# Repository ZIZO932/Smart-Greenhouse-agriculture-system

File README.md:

# Smart Greenhouse

A greenhouse prototype I built to monitor growing conditions and control pumps, fans, lighting, and temperature hardware. I used sweet basil as the main crop for testing.

The project changed quite a bit between the CAD and the assembled version. The original design used a Raspberry Pi Pico W, and I switched to an ESP32 during the build after damaging the Pico. Both versions are kept in this repo.

## Why I built it

I wanted to connect sensor readings to something the greenhouse could actually do: water the soil, switch on a fan, or adjust the lights. Fitting the tanks, pumps, electronics, and growing bed into one structure was a big part of the work too.

## The layout

The design has three main stacked sections, plus a camera track around the top:

- **Tanks and pumps:** a 5 L water tank and three 1 L nutrient tanks, each with its own pumping line.
- **Electronics:** the controller, power distribution, sensor connections, and relay circuitry.
- **Growing bed:** the soil and plants, with tubing routed up from the tanks.
- **Camera track:** a planned moving camera platform for taking pictures around the plants.

The CAD used a transparent bed. For the physical prototype, I built the frame from MDF and used a polyethylene cover for the growing layer.

[CAD files](CAD/) include the assembly and a ZIP archive. The larger STEP model is also [on Google Drive](https://drive.google.com/file/d/1caedlcHiUJ2DHqxGwvVZIDkTWpKjw0eq/view?usp=drive_link).

## Electronics

The original PCB design uses a ULN2803A to drive the relays, with separate power rails for the controller, sensors, and higher-power hardware. The sensor setup includes a BH1750 light sensor, DS18B20 temperature sensing, capacitive soil moisture sensing, and an RS-485 connection for an NPK sensor through a MAX485.

I had to fix relay footprints and adjust the routing while working through the board design.

## Building it

The first frame used nails and didn't hold the weight properly. I rebuilt the joints with screws, then routed the pumps and tubing through the layers.

I assembled the regulated power supply and wired the sensors and relay-controlled hardware. This was also where I damaged the Pico and moved to the ESP32. My build notes record a six-hour integrated test of the sensors and actuators.

## Dashboard and code

The dashboard work uses MQTT, Flask, and MySQL to collect and display readings. Grafana is shown in the build documentation too.

There are a few different stages in the uploaded code:

| File or folder | What it contains |
| --- | --- |
| [Firmware/main.py](Firmware/main.py) | Pico MicroPython code for sensor reading, relay control, and UART communication with a Pi Zero |
| [website/app.py](website/app.py) | Flask app that receives MQTT messages, stores readings in MySQL, and serves dashboard endpoints |
| [website/final_code_10204.ino](website/final_code_10204.ino) | ESP32 code excerpt with sensor functions, relay helpers, and plant profiles |
| [code parts](code%20parts/) | Other Arduino and MQTT snippets from development |
| [templates](templates/) | Dashboard HTML |

The ESP32 excerpt currently generates sample NPK values in `updateFakeNPK()`. Those values aren't live nutrient measurements. It also doesn't include `setup()` and `loop()`, so the uploaded excerpt isn't a complete flashable sketch.

The Flask app expects `templates/index.html` next to the app, while the uploaded HTML is named `templates/index (1).html` at the repo root. That path needs matching before running the dashboard locally. Broker addresses and database settings also need to match the local setup.

## Camera and disease detection

I planned a Pi Zero 2 W and Camera V2 platform that moves around the plants, takes images, and parks between scans. The proposed scan interval was 30 minutes, with a model trained using the [New Plant Diseases Dataset](https://www.kaggle.com/datasets/vipoooool/new-plant-diseases-dataset).

The repo doesn't include trained model files or disease-detection results yet. This part is documented as a planned extension of the monitoring system.

## Original parts estimate

This is the parts list from the original design stage, including the Pico and camera hardware. Prices are recorded estimates from that stage.

| Name | Cost Per Item (USD) | Quantity | Total (USD) | Link | Distributor |
| :--- | :--- | :--- | :--- | :--- | :--- |
| **Water pump** | 5.57 | 4 | 22.28 | [Link](https://www.ram-e-shop.com/shop/dc-pump-240l-water-pump12vdc-ultra-quiet-brushless-240l-h-7953) | Ram Electronics |
| **PCB Fabrication** | 5.74 | 1 | 5.74 | [Link](https://jlcpcb.com) | JLCPCB |
| **Pin Header 1x04** | 0.12 | 2 | 0.24 | [Link](https://makerselectronics.com/product/pin-headers-male-2-54mm-5pin-straight-black-11mm/) | Makers Electronics |
| **Pin Header 1x02** | 0.10 | 7 | 0.67 | [Link](https://makerselectronics.com/product/pin-headers-male-2-54mm-5pin-straight-black-11mm/) | Makers Electronics |
| **Ceramic Cap** | 0.04 | 10 | 0.38 | [Link](https://makerselectronics.com/product/ceramic-capacitor-100nf-50v/) | Makers Electronics |
| **Electrolytic Cap** | 0.10 | 4 | 0.40 | [Link](https://makerselectronics.com/product/capacitor-10uf-25v-4x7mm/) | Makers Electronics |
| **Resistor** | 0.04 | 10 | 0.40 | [Link](https://makerselectronics.com/product/carbon-resistor-10k%cf%89-2w-through-hole/) | Makers Electronics |
| **12V 5A Power Adapter** | 5.74 | 1 | 5.74 | [Link](https://makerselectronics.com/product/adapter-12v-3a-3/) | Makers Electronics |
| **Barrel Jack** | 0.29 | 1 | 0.29 | [Link](https://store.fut-electronics.com/products/dc-barrel-female-jack?_pos=2&_sid=9cbb68bec&_ss=r) | Future Electronics Egypt |
| **DIP-18 Socket** | 3.16 | 1 | 3.16 | [Link](https://store.fut-electronics.com/search?type=product&q=DIP-18+7.62mm) | Future Electronics Egypt |
| **Relay** | 1.34 | 7 | 9.38 | [Link](https://www.amazon.eg/-/en/Generic-12V-Relay-SRD-12VDC-SL-C-Automatic/dp/B09GNYCBJ8) | Amazon Egypt |
| **Schottky Diode** | 0.15 | 1 | 0.15 | [Link](https://store.fut-electronics.com/products/copy-of-diode-1n5408-3a-1000v-high-current-rectifier?_pos=1&_sid=7c0e00b0d&_ss=r) | Future Electronics Egypt |
| **Inductor** | 0.02 | 1 | 0.02 | [Link](https://makerselectronics.com/product/inductor-330uh-0510-1w/?srsltid=AfmBOopEyPfXRbjQeAZuTj9z0SJHXyytV2tzQKyfccnhfVPX7rr7i2Ne) | Makers Electronics Egypt |
| **NPK Soil Sensor** | 61.26 | 1 | 61.26 | [Link](https://store.fut-electronics.com/products/soil-npk-nitrogen-phosphorus-potassium-nutrient-sensor?_pos=1&_sid=cc849b4cb&_ss=r) | Future Electronics Egypt |
| **Soil Moisture Sensor** | 1.91 | 1 | 1.91 | [Link](https://www.ram-e-shop.com/shop/sen-soil-c-capacitive-analog-soil-moisture-sensor-v2-0-sku-soil-c-8116?srsltid=AfmBOookvggy4W1wl8oSb-pGGNBmixARQOTydpFUzx5W_-lss_Y-4-94) | RAM Electronics |
| **Light Sensor** | 3.73 | 1 | 3.73 | [Link](https://store.fut-electronics.com/products/digital-light-intensity-module) | Future Electronics Egypt |
| **Temp Sensor (air)** | 0.86 | 1 | 0.86 | [Link](https://makerselectronics.com/product/ds18b20-temperature-sensor-to-92/) | Makers Electronics Egypt |
| **Temp Sensor (soil)** | 1.63 | 1 | 1.63 | [Link](https://www.ram-e-shop.com/ar/shop/wire-ds18b20-ds18b20-waterproof-temperature-sensor-original-chip-7175) | RAM Electronics |
| **Darlington Driver** | 0.46 | 1 | 0.46 | [Link](https://makerselectronics.com/product/uln2803apg-darlington-transistor-arrays-dip-18-brand-toshiba/) | Makers Electronics |
| **RS485 Transceiver** | 0.55 | 1 | 0.55 | [Link](https://uge-one.com/product/max485-rs-485-transceiver-dip8/) | UGE Electronics Egypt |
| **Raspberry Pi Camera V2** | 15.31 | 1 | 15.31 | [Link](https://www.ram-e-shop.com/ar/shop/rpi-v2-camera-raspberry-pi-camera-module-v2-official-8-mp-hd-imx219-official-6887) | Ram Electronics |
| **LDO Regulator** | 0.06 | 1 | 0.06 | [Link](https://www.ram-e-shop.com/ar/shop/lt1117-3-3v-ams1117-3-3v-6628) | Ram Electronics Egypt |
| **Buck Converter IC** | 0.77 | 1 | 0.77 | [Link](https://makerselectronics.com/product/lm2596t-5-0-buck-fixed-40v-5v-3a-to-220-5l-dc-dc-converters-dip-ic/) | Makers Electronics Egypt |
| **Raspberry Pi Zero 2W** | 38.28 | 1 | 38.28 | [Link](https://devboardsmarket.com/products/raspberry-pi-zero-2-w) | DEV boards |
| **Raspberry Pi Pico W** | 16.27 | 1 | 16.27 | [Link](https://www.ram-e-shop.com/ar/shop/rpi-pico-w-raspberry-pi-pico-w-wifi-8524) | RAM electronics |
| **GRAND TOTAL** | | | **$189.94** | | |

## More files

- [Circuit, PCB, and Gerber files](Circuit%20%28Schematic%20and%20pcb%29/)
- [BOM](BOM.csv)
- [Build journal](JOURNAL%20%285%29.md)
- [Database schema](website/database.sql)

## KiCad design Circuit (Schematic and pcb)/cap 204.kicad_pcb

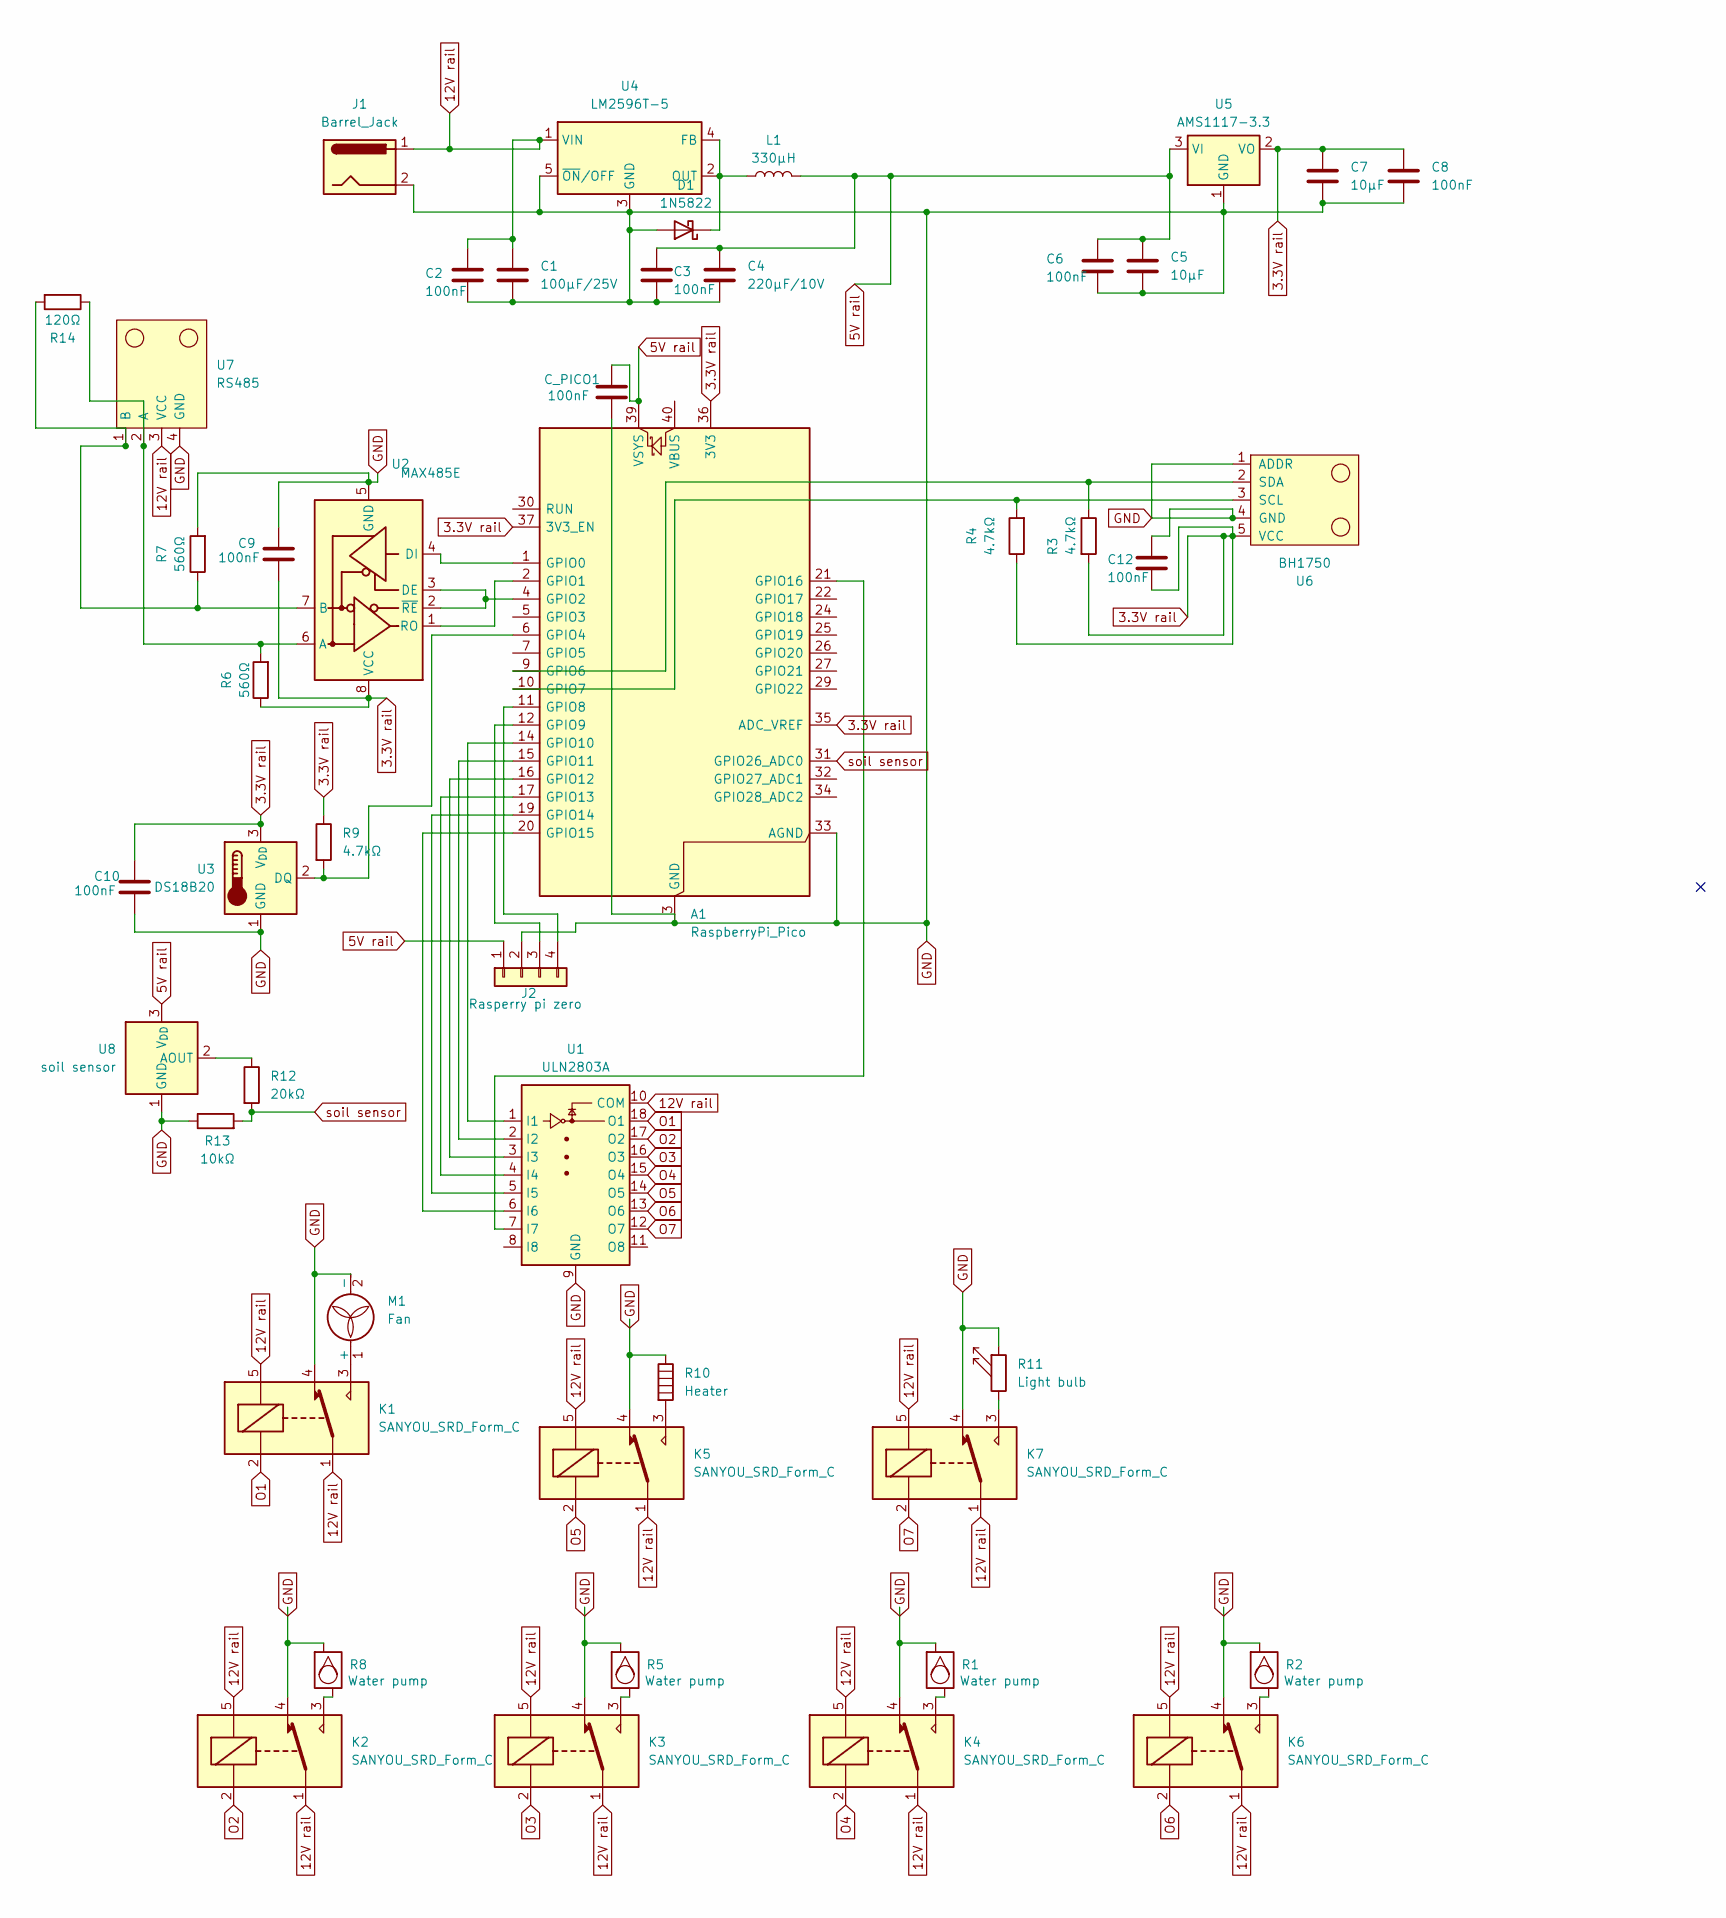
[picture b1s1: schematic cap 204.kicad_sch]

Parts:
A1: RaspberryPi_Pico; RaspberryPi_Pico_Common_Unspecified
C1: 100µF/25V; CP_Radial_D6.3mm_P2.50mm
C2, C3, C6, C8, C9, C10, C12: 100nF; C_Disc_D3.0mm_W1.6mm_P2.50mm
C4: 220µF/10V; CP_Radial_D8.0mm_P3.50mm
C5, C7: 10µF; CP_Radial_D5.0mm_P2.50mm
C_PICO1: 100nF; C_Disc_D3.0mm_W1.6mm_P2.50mm
D1: 1N5822; D_DO-201AD_P15.24mm_Horizontal
J1: Barrel_Jack; L_Axial_L7.0mm_D3.3mm_P10.16mm_Horizontal_Fastron_MICC
J2: Rasperry pi zero; PinHeader_1x04_P2.54mm_Vertical
K1, K2, K3, K4, K5, K6, K7: SANYOU_SRD_Form_C; Relay_SPDT_SANYOU_SRD_Series_Form_C
L1: 330µH; L_Axial_L7.0mm_D3.3mm_P10.16mm_Horizontal_Fastron_MICC
M1: Fan; PinHeader_1x02_P2.54mm_Vertical
R1, R2, R5, R8: Water pump; PinHeader_1x02_P2.54mm_Vertical
R3, R4, R9: 4.7kΩ; R_Axial_DIN0204_L3.6mm_D1.6mm_P7.62mm_Horizontal
R6, R7: 560Ω; R_Axial_DIN0204_L3.6mm_D1.6mm_P7.62mm_Horizontal
R10: Heater; PinHeader_1x02_P2.54mm_Vertical
R11: Light bulb; PinHeader_1x02_P2.54mm_Vertical
R12: 20kΩ; R_Axial_DIN0204_L3.6mm_D1.6mm_P7.62mm_Horizontal
R13: 10kΩ; R_Axial_DIN0204_L3.6mm_D1.6mm_P7.62mm_Horizontal
R14: 120Ω; R_Axial_DIN0204_L3.6mm_D1.6mm_P7.62mm_Horizontal
U1: ULN2803A; DIP-18_W7.62mm
U2: MAX485E; SOIC-8_3.9x4.9mm_P1.27mm
U3: DS18B20; TO-92_Inline
U4: LM2596T-5; TO-220-5_P3.4x3.7mm_StaggerOdd_Lead3.8mm_Vertical
U5: AMS1117-3.3; SOT-223-3_TabPin2
U6: BH1750; module_bh1750
U7: RS485; PinHeader_1x04_P2.54mm_Vertical
U8: soil sensor; TO-92_Inline

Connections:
3.3V rail: A1.35 (ADC_VREF), A1.36 (3V3), A1.37 (3V3_EN), C7.1, C8.1, C9.2, C10.1, C12.2, R3.2, R4.1, R6.1, R9.1, U2.8 (VCC), U3.3 (V_{DD}), U5.2 (VO), U6.5 (VCC)
5V rail: A1.39 (VSYS), C3.1, C4.1, C5.1, C6.1, C_PICO1.1, J2.1, L1.2, U5.3 (VI), U8.3 (V_{DD})
12V rail: C1.1, C2.1, J1.1, K1.1, K1.5, K2.1, K2.5, K3.1, K3.5, K4.1, K4.5, K5.1, K5.5, K6.1, K6.5, K7.1, K7.5, U1.10 (COM), U4.1 (VIN), U7.3 (VCC)
GND: A1.3 (GND), A1.8 (GND), A1.13 (GND), A1.18 (GND), A1.23 (GND), A1.28 (GND), A1.33 (AGND), A1.38 (GND), C1.2, C2.2, C3.2, C4.2, C5.2, C6.2, C7.2, C8.2, C9.1, C10.2, C12.1, C_PICO1.2, D1.2 (A), J1.2, J2.2, K1.4, K2.4, K3.4, K4.4, K5.4, K6.4, K7.4, M1.2 (-), R1.1, R2.1, R5.1, R7.2, R8.1, R10.1, R11.1, R13.1, U1.9 (GND), U2.5 (GND), U3.1 (GND), U4.3 (GND), U4.5 (~ON/OFF), U5.1 (GND), U6.1 (ADDR), U6.4 (GND), U7.4 (GND), U8.1 (GND)
unnamed: A1.1 (GPIO0), U2.4 (DI)
unnamed: A1.2 (GPIO1), U2.1 (RO)
unnamed: A1.4 (GPIO2), U2.2 (~RE), U2.3 (DE)
unnamed: A1.6 (GPIO4), R9.2, U3.2 (DQ)
unnamed: A1.9 (GPIO6), R3.1, U6.2 (SDA)
unnamed: A1.10 (GPIO7), R4.2, U6.3 (SCL)
unnamed: A1.11 (GPIO8), J2.4
unnamed: A1.12 (GPIO9), J2.3
unnamed: A1.14 (GPIO10), U1.1 (I1)
unnamed: A1.15 (GPIO11), U1.2 (I2)
unnamed: A1.16 (GPIO12), U1.3 (I3)
unnamed: A1.17 (GPIO13), U1.4 (I4)
unnamed: A1.19 (GPIO14), U1.5 (I5)
unnamed: A1.20 (GPIO15), U1.6 (I6)
unnamed: A1.21 (GPIO16), U1.7 (I7)
unnamed: D1.1 (K), L1.1, U4.2 (OUT), U4.4 (FB)
unnamed: K2.3, R8.2
unnamed: K3.3, R5.2
unnamed: K4.3, R1.2
unnamed: K5.3, R10.2
unnamed: K6.3, R2.2
unnamed: K7.3, R11.2
unnamed: K1.3, M1.1 (+)
unnamed: R6.2, R14.1, U2.6 (A), U7.2 (A)
unnamed: R7.1, R14.2, U2.7 (B), U7.1 (B)
unnamed: R12.1, U8.2 (AOUT)
O1: K1.2, U1.18 (O1)
O2: K2.2, U1.17 (O2)
O3: K3.2, U1.16 (O3)
O4: K4.2, U1.15 (O4)
O5: K5.2, U1.14 (O5)
O6: K6.2, U1.13 (O6)
O7: K7.2, U1.12 (O7)
soil sensor: A1.31 (GPIO26_ADC0), R12.2, R13.2

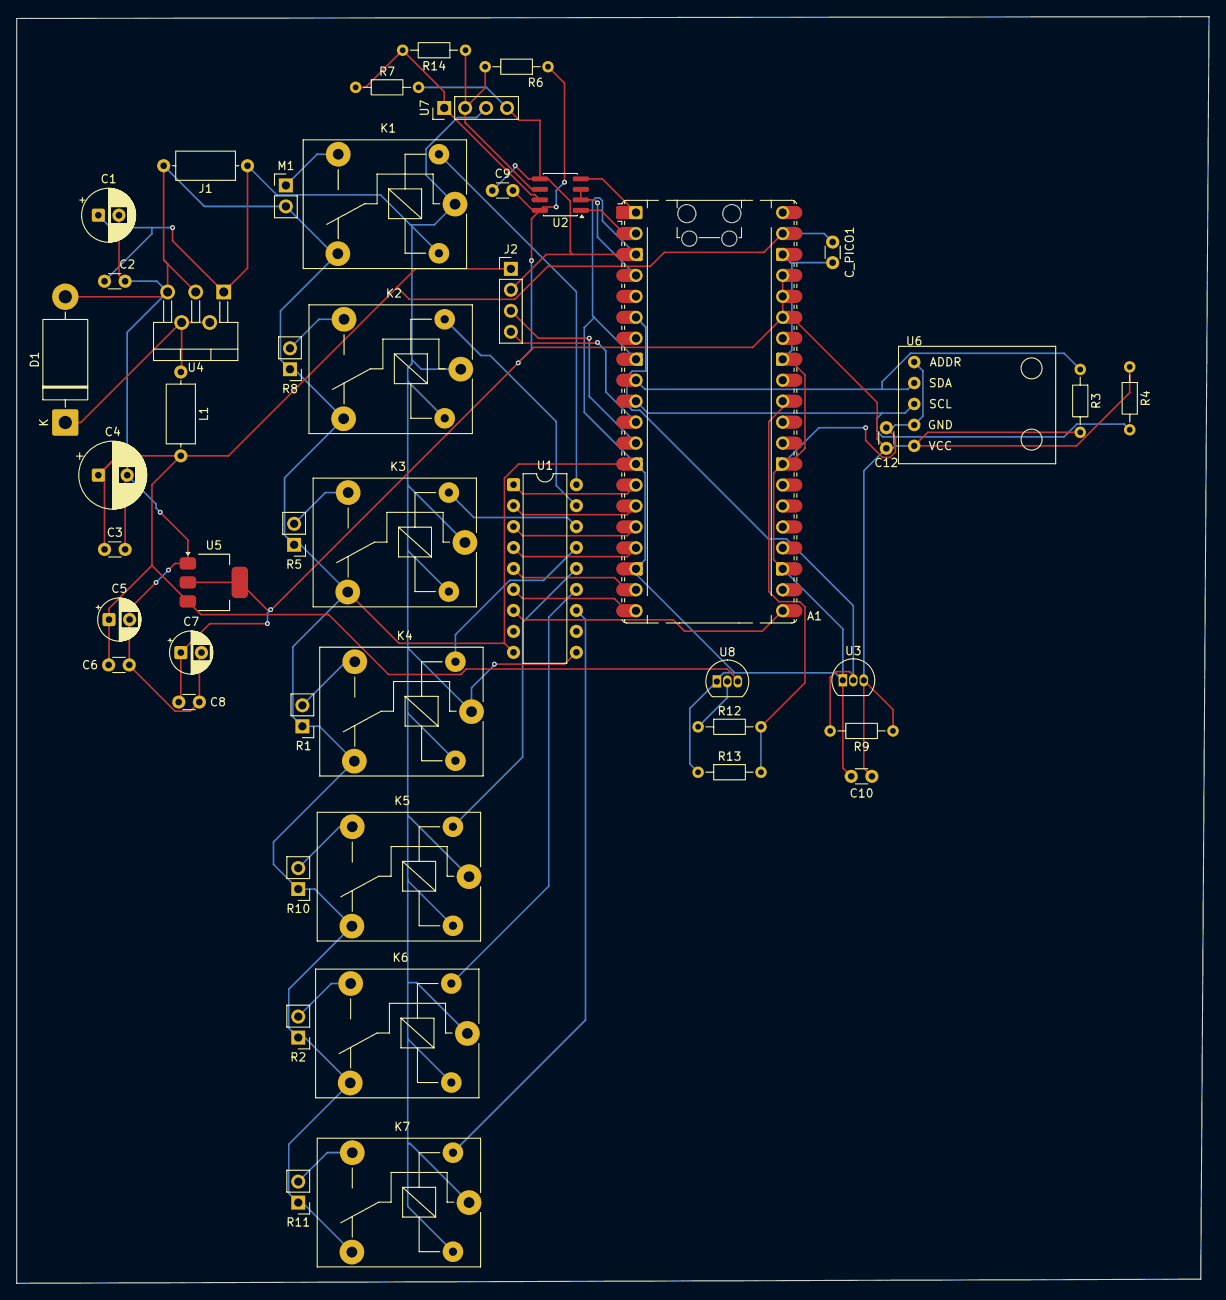
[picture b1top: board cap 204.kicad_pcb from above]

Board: 2 copper layers, 144.5 x 153.5 mm, 47 parts (0 on the bottom side), 38 nets.
